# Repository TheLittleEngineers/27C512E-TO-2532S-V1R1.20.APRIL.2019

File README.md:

# 27C512E-TO-2532S-V1R1.20.APRIL.2019
<p align="center">
TheLittleEngineers.org-27C512E-TO-2532S-V1R1.20.APRIL.2019
27C512 E.P.R.O.M. TO TMS2532 SOCKET CONVERTER.
(C) 20 April 2019 and 01 June 2019 by: Robert Allen Turner
http://www.TheLittleEngineers.org/
https://github.com/TheLittleEngineers
</p>
<p align="justify">
This product is intended to allow a 27512 or 27C512 EPROM to be placed into a TMS2532 EPROM socket. The 27512 is divided into 16 banks of 4Kbytes via the four jumpers at the bottom of the socket.

Released under a Creative Commons Attribution-ShareAlike 4.0 International (CC BY-SA 4.0) License, 01 June 2019 In Memory of my Father, Robert Embry Turner, 1945 - 2019. Rest In Peace. I LOVE YOU DAD!
</p>
<p align="center">
Archive name: "TheLittleEngineers.org-27C512E-TO-2532S-V1R1.20.APRIL.2019"
</p>
This is an update to the "TheLittleEngineers.org-27C512E-TO-2532S-V1R0.20.APRIL.2019" repository which resides at this url:
https://github.com/TheLittleEngineers/27C512E-TO-2532S-V1R0
This update was made due to the fact that I was not very pleased with the initial Printed Circuit Boards that resulted from the original design. Although functional, the production of the Printed Circuit Boards was inconsistent between different manufacturers. This was due to a problem in the dimension layer of the original design and so I have created this new design to eliminate the inconsistencies.

This version should provide much better results.

Please note: This is derived from an original design by "Little" John Eric and/or his father "Big" John Robert (J.R.) by "Uncle" Robert Allen. It should be thoroughly scrutinized and verified prior to actual use of any kind. DISCLAIMER: The following article is provided for informational purposes only. Any attempt to modify your computer without the proper skills to do so may void your computer. Any attempt to modify your computer without unplugging it first may void you. This Information is provided "as-is" with no guarantee of fitness for any purpose, either explicit or implied. We disclaim any and all responsibility for losses incurred through the use of this information. By using this information, you are deemed to have accepted these conditions of use, and you agree NOT to sue us. CLARIFICATION: The above disclaimer states as plainly as possible that if you decide to make use of any of the information contained within this document that you do so at your own risk. Designing hardware for the CoCo (ColorComputer) and other vintage hardware is a hobby of ours and is not motivated by any desire of profits. As this is a not for profit venture, obviously we can't afford not to disclaim the use of this information.

The GitHub home of this project is available at the following url:
https://github.com/TheLittleEngineers/27C512E-TO-2532S-V1R1.20.APRIL.2019

This design is available at OSHPark with the following urls:
https://oshpark.com/shared_projects/JmUiHyi1 (EAGLE .brd)
https://oshpark.com/shared_projects/4RvjjYdM (KiCAD .kicad_pcb)
Note that the KiCAD version has been imported using the EAGLE import function of the Version 5.x of KiCAD. As such, it may be potentially problematic.

<!DOCTYPE html>
<html>
<head>

<meta name="Author" content="Robert &quot;The R.A.T.&quot; Allen Turner">
<meta name="GENERATOR" content="Tandy Radio Shack TRS-80 Color Computer 3">
<meta name="ProgId" content="TeleWriter-128.by.Bob.Van.der.Poel.for.Cognitec">
<meta http-equiv="Content-Type" content="text/html; charset=UTF-8">
<meta http-equiv="Content-Language" content="en-us">
<meta name="viewport" content="width=device-width, initial-scale=1">
<!--
<!meta http-equiv="Content-Type" content="text/html; charset=windows-1252">
This HTML is a veritable train wreck, however, it seems to get the job done on 24 September 2020 and beyond
-->

</head>

<body style="background-color:WhiteSmoke;">

<!-- Top Row -->
<center>
<h3 style="text-align: center; color: Black;">This page created: May 26, 2019, last updated: September 24, 2020. 
</center>
<p align="center">
<font size="6"><a href="http://www.TheLittleEngineers.org/" target="_blank">The</a> <a href="http://www.TheLittleEngineers.org/" target="_blank">Little</a> <a href="http://www.TheLittleEngineers.org/" target="_blank">Engineers</a> in conjunction with <a href="http://www.RetroATX.com" target="_blank">Retro</a><u>-</u><a href="http://www.Retro-ATX.com" target="_blank">ATX</a><br></font>
<font size="5"><em><b><a href="https://www.facebook.com/OurLittleEngineers/" target="_blank">Pulling</a> <a href="https://www.facebook.com/groups/985537051651794/" target="_blank">The</a> <a href="https://www.facebook.com/groups/566741160795144/" target="_blank">Past</a> <a href="https://www.facebook.com/TheLittleEngineers.org" target="_blank">Into</a> <a href="https://www.facebook.com/tincansandducttape/" target="_blank">The</a> <a href="https://www.facebook.com/Tin-Cans-Duct-Tape-728969003939754/" target="_blank">Present</a> <a href="https://www.facebook.com/groups/1654785514796788/" target="_blank">For</a> <a href="https://www.facebook.com/groups/1828354620822631/" target="_blank">The</a> <a href="https://www.facebook.com/groups/1451396811790867/" target="_blank">Future</a></b></em><br></font>
</p>
<p align="justify"><a href="http://www.TheLittleEngineers.org/" target="_blank">The</a> <a href="http://www.TheLittleEngineers.org/" target="_blank">Little</a> <a href="http://www.TheLittleEngineers.org/" target="_blank">Engineers</a> is a project began in 2011 by <a href="mailto:TheLittleEngineers@OutLook.com" target="_blank">Robert</a> <a href="mailto:LittleEngineer_RAT@OutLook.com" target="_blank">Allen</a> <a href="mailto:OurLittleEngineers@gMail.com" target="_blank">Turner</a> (hereafter, <a href="mailto:LittleEngineer.RAT@gMail.com" target="_blank">I</a>, <a href="mailto:TinCansAndDuctTape@gMail.com" target="_blank">Me</a>, <a href="mailto:CannedLogic@gMail.com" target="_blank">My</a>, <a href="mailto:TinCansAndDuctTape@OutLook.com" target="_blank">Author</a>, or <a href="mailto:LittleEngineer.RAT@OutLook.com" target="_blank">&quot;The R.A.T.&quot;</a>), for the benefit of foster children and their families (foster and biological). The original intent was simply to provide a means, in the form of donated cameras, of creating videos with the foster families such that the biological parents did not completely miss out on their children growing up. Providing simple to construct kits (electronics, arts, crafts, etcetera) seemed a logical choice as subject matter for such videos and these types of activities have the benefit of being educational. It is thus that those types of projects are primarily what <a href="mailto:LittleEngineer.RAT@OutLook.com" target="_blank">I</a> attempt to develop for use in such videos. This is a difficult, time consuming and expensive undertaking. Each case must be handled on an individual basis and any such videos and communications must be scrutinized and approved on a per case basis by the case workers, et alia in charge. Although this makes such an undertaking extremely difficult, it is a necessity in order to protect the children. Some are, after all, being protected from abusive family members and so there has to be a very strict set of protocols in place. This has prevented me from fully launching <a href="https://www.facebook.com/OurLittleEngineers/" target="_blank">The</a> <a href="https://www.facebook.com/groups/985537051651794/" target="_blank">Little</a> <a href="https://www.facebook.com/TheLittleEngineers.org" target="_blank">Engineers</a> over the past eight years, but I remain fully committed to the project with the intent of seeing it through to a fully operational entity.
</p>
<p align="justify"><a href="http://www.RetroATX.com" target="_blank">Retro</a><u>-</u><a href="http://www.Retro-ATX.com" target="_blank">ATX</a> was conceived with the sole purpose of creating &quot;ATX form factor&quot; versions of various <em>classic</em> and <i>vintage</i> computing and other systems. Such a system might be an Altair 8800 &quot;clone&quot; in an ATX or &micro;ATX form factor. Certainly, a system compatible with the Tandy Radio Shack TRS-80 Model II, 12, 16 and 6000 line of computers is planned, as are ATX or &micro;ATX versions of the following systems:<ul align="justify"><li align="justify">Sinclair QL</li><li align="justify">Dragon D64 and D200</li><li align="justify">Dragon Alpha</li><li align="justify">Dragon Beta</li><li align="justify">Tandy Color Computer 3</li><li align="justify">Mattel Intellivision &quot;Keyboard Component&quot;</li><li align="justify">Aamber Pegasys</li><li align="justify">MicroBox ][</li><li align="justify">Various Frank Hogg Laboratories Systems, including:<ul align="justify"><li align="justify">FHL &quot;K-Buss&quot; backplanes of many sizes and configurations</li><li align="justify">FHL Tomcat Series, including:<ul align="justify"><li align="justify">FHL TC-9 6809 CPU board</li><li align="justify">FHL TC-9 I/O board</li><li align="justify">FHL TC-70 68070 CPU board</li><li align="justify">FHL TC-70 I/O and all other boards</li></ul></li></ul></li><li align="justify">GIMIX 6800/6809 Series Motherboards</li><li align="justify">GIMIX 6800/6809 Series CPU boards</li><li align="justify">GIMIX 6800/6809 Series Peripheral Cards</li><li align="justify">SWTPC 6800/6809 Series Motherboards</li><li align="justify">SWTPC 6800/6809 Series CPU boards</li><li align="justify">SWTPC 6800/6809 Series Peripheral Cards</li></ul>
</p>
<p align="justify">The above list represents just some of the systems that are planned for reimplementation by <a href="http://www.RetroATX.com" target="_blank">Retro</a><u>-</u><a href="http://www.Retro-ATX.com" target="_blank">ATX</a>. Any suggestions for other systems and features are welcomed. The MicroBox ][, Aamber Pegasus and Frank Hogg Laboratory systems are a priority at present, although this may change based upon feedback received. Undertaking any one of the above projects is a monumental task, requiring the expenditure of many hours of work and yet we fully intend to complete each and every one of those projects as time and resources allow. It is very unlikely that we will be able to complete all of these projects without the assistance of the many members of the <em>&quot;Vintage Computing Community&quot;.</em> We are in dire need of donations of any of the following items:<ul align="justify"><li align="justify">SCHEMATICS, documentations, Theory of Operations, etcetera of any and all of the above listed equipment</li><li align="justify">Any of the above hardware and peripherals that you may no longer have need of, functional or not</li><li align="justify">Your expertise, experience, opinions, engineering and other skills, etcetera</li></ul><b>Any items of interest, from the above list(s) or otherwise may be delivered to:</b>
</p>
<p align="center"><b>The Little Engineers Project/RetroATX.com<br>C/O Robert Turner<br>69 Lilly Lane<br>Pell City, AL 35125</b></p>
<p align="justify">Your continued encouragement and <a href="#support">support</a> are greatly appreciated. Other methods of <a href="#digitalcurrency">potential</a> <a href="#patreon">support</a> are contained <a href="#support">further</a> into this <a href="#support">document</a>. Thank You and God Bless.</p>
 
<p align="justify"><b>The logos, names and other material relating to <a href="https://www.facebook.com/OurLittleEngineers/" target="_blank">The</a> <a href="https://www.facebook.com/groups/985537051651794/" target="_blank">Little</a> <a href="https://www.facebook.com/TheLittleEngineers.org" target="_blank">Engineers</a>, <a href="http://www.TheLittleEngineers.org/" target="_blank">TheLittleEngineers.org</a>, <a href="http://www.RoboCircuits.org/" target="_blank">RoboCircuits</a>, <a href="http://www.RoboCircuits.org/" target="_blank">RoboCircuits.org</a>, <a href="https://www.facebook.com/tincansandducttape/" target="_blank">Tin</a> <a href="https://www.facebook.com/groups/1654785514796788/" target="_blank">Cans</a> <a href="https://www.facebook.com/Tin-Cans-Duct-Tape-728969003939754/" target="_blank">And</a> <a href="https://www.facebook.com/groups/1828354620822631/" target="_blank">Duct</a> <a href="https://www.facebook.com/groups/228910954180459/" target="_blank">Tape</a>, <a href="http://www.tincansandducttape.com/" target="_blank">TinCansAndDuctTape.com</a>, <a href="http://www.tcadt.com/" target="_blank">TCADT</a>, <a href="http://www.tcadt.com/" target="_blank">TCADT.com</a>, <a href="http://www.CannedLogic.com/" target="_blank">Canned Logic</a>, <a href="http://www.CannedLogic.com/" target="_blank">CannedLogic.com</a>, <a href="http://www.RetroATX.com/" target="_blank">RetroATX</a>, <a href="http://www.RetroATX.com/" target="_blank">RetroATX.com</a>, <a href="http://www.Retro-ATX.com/" target="_blank">Retro-ATX</a>, <a href="http://www.Retro-ATX.com/" target="_blank">Retro-ATX.com</a>, <a href="http://www.TheLittleEngineers.org/pages/reference/20200112/ZombieSoftwareSystems" target="_blank">Zombie</a> <a href="http://www.TheLittleEngineers.org/pages/reference/20200112/ZombieSoftwareSystems" target="_blank">Software</a> <a href="http://www.TheLittleEngineers.org/pages/reference/20200112/ZombieSoftwareSystems" target="_blank">Systems</a>, <a href="http://www.TheLittleEngineers.org/pages/reference/20200112/BinarySystems" target="_blank">Binary</a> <a href="http://www.TheLittleEngineers.org/pages/reference/20200112/BinarySystems" target="_blank">Systems</a>, <a href="http://www.GIMEchip.com/" target="_blank">GIMEchip</a> and <a href="http://www.GIMEchip.com/" target="_blank">GIMEchip.com</a> are the sole property of <a href="https://www.facebook.com/TheLittleEngineers.org" target="_blank">Robert</a> <a href="mailto:TheLittleEngineers@OutLook.com" target="_blank">Allen</a> <a href="https://www.facebook.com/TinCansDuctTape" target="_blank">Turner</a> with <em>All Rights Reserved</em>.</b> The rights to the <a href="http://www.GIMEchip.com/" target="_blank">GIMEchip.com</a> domain and <a href="https://www.github.com/TheLittleEngineers?tab=repositories" target="_blank">products</a> were acquired by the <a href="https://www.facebook.com/TheLittleEngineers.org" target="_blank">author</a> on 25 December 2018 from my brother and his son, the former owners/operators of <a href="http://www.GIMEchip.com/" target="_blank">GIMEchip.com</a>. Please note that the author is unable to answer any inquiries, including those of support or otherwise, in relation to <a href="http://www.GIMEchip.com/" target="_blank">GIMEchip.com</a> prior to his acquisition of same on 25 December 2018. This is primarily because the author posseses no knowlege of the site operation prior to that time. Although I have been provided with a large number of files that were originally contained on the website, it is unlikely that I will resurrect <a href="http://www.GIMEchip.com/" target="_blank">GIMEchip.com</a> other than perhaps as a <a href="http://www.TheLittleEngineers.org/WebSites/GIMEchip/" target="_blank">page</a> on <a href="http://www.TheLittleEngineers.org/WebSites/GIMEchip/" target="_blank">one</a> of my other websites. These files are mostly HTML page files and C.A.D. files of the products designed and developed by my nephew and his father, and very little else. As part of the acquisition agreement, all products previously produced by <a href="http://www.GIMEchip.com/" target="_blank">GIMEchip.com</a> are to be released under a <a href="http://www.TheLittleEngineers.org/pages/reference/20200112/CreativeCommons/CCBYSA.htm" target="_blank">Creative Commons Attribution-ShareAlike 4.0 International</a> <a href="http://www.TheLittleEngineers.org/pages/reference/20200112/CreativeCommons/CCBYSALegalCode.htm" target="_blank">(CC BY-SA 4.0)</a> License, as time and resources permit. Although many of these projects are somewhat interesting, none of them seem particularly useful or revolutionary.</p>
<p align="center">
<font size="6">DISCLAIMER:<br></font>
<font size="5"><em>Please Read Carefully.<br></em></font>
</p>
<p align="justify">This information is provided for informational purposes only. Any attempt to modify your equipment (including, but not limited to kit assembly) without the proper skills to do so may void your equipment. Any attempt to modify your equipment without unplugging it first may void you. This Information is provided "as-is" with no guarantee of fitness for any purpose, either explicit or implied. We disclaim any and all responsibility for losses incurred through the use of this information. Included with this information may be one or more C.A.D. Libraries, such as for E.A.G.L.E., KiCAD, etcetera. Any such C.A.D. libraries, except as may be noted are released under a <a href="http://www.TheLittleEngineers.org/pages/reference/20200112/CreativeCommons/CCBYSA.htm" target="_blank">Creative Commons Attribution-ShareAlike 4.0 International</a> <a href="http://www.TheLittleEngineers.org/pages/reference/20200112/CreativeCommons/CCBYSALegalCode.htm" target="_blank">(CC BY-SA 4.0)</a> License. You may use these libraries in your own projects, however, please take note that we CANNOT guarantee the accuracy of the components (nor any part of these libraries and/or information). We make NO guarantees that the components, footprints or schematic symbols contained in these libraries are flawless, and we make no promises of fitness for production, prototyping or any other purpose. These libraries and/or information are provided for informational purposes only, and are used at your own discretion. By downloading these libraries and/or information, you agree that we cannot be held responsible for faulty PCBs (Printed Circuit Boards). <b>You should always check the footprints with a 1:1 printout.</b> Neither Robert Allen Turner, <a href="https://www.facebook.com/OurLittleEngineers/" target="_blank">The</a> <a href="https://www.facebook.com/groups/985537051651794/" target="_blank">Little</a> <a href="https://www.facebook.com/TheLittleEngineers.org" target="_blank">Engineers</a>, <a href="http://www.TheLittleEngineers.org/" target="_blank">TheLittleEngineers.org</a>, <a href="https://www.facebook.com/tincansandducttape/" target="_blank">Tin</a> <a href="https://www.facebook.com/groups/1654785514796788/" target="_blank">Cans</a> <a href="https://www.facebook.com/Tin-Cans-Duct-Tape-728969003939754/" target="_blank">And</a> <a href="https://www.facebook.com/groups/1828354620822631/" target="_blank">Duct</a> <a href="https://www.facebook.com/groups/228910954180459/" target="_blank">Tape</a>, <a href="http://www.tincansandducttape.com/" target="_blank">TinCansAndDuctTape.com</a>, <a href="http://www.tcadt.com/" target="_blank">TCADT</a>, <a href="http://www.tcadt.com/" target="_blank">TCADT.com</a>, <a href="http://www.CannedLogic.com/" target="_blank">Canned Logic</a>, <a href="http://www.CannedLogic.com/" target="_blank">CannedLogic.com</a>, <a href="http://www.RetroATX.com/" target="_blank">RetroATX</a>, <a href="http://www.RetroATX.com/" target="_blank">RetroATX.com</a>, <a href="http://www.Retro-ATX.com/" target="_blank">Retro-ATX</a>, <a href="http://www.Retro-ATX.com/" target="_blank">Retro-ATX.com</a>, <a href="http://www.RoboCircuits.org/" target="_blank">RoboCircuits</a>, <a href="http://www.RoboCircuits.org/" target="_blank">RoboCircuits.org</a>, <a href="http://www.TheLittleEngineers.org/pages/reference/20200112/ZombieSoftwareSystems" target="_blank">Zombie</a> <a href="http://www.TheLittleEngineers.org/pages/reference/20200112/ZombieSoftwareSystems" target="_blank">Software</a> <a href="http://www.TheLittleEngineers.org/pages/reference/20200112/ZombieSoftwareSystems" target="_blank">Systems</a>, <a href="http://www.TheLittleEngineers.org/pages/reference/20200112/BinarySystems" target="_blank">Binary</a> <a href="http://www.TheLittleEngineers.org/pages/reference/20200112/BinarySystems" target="_blank">Systems</a>, <a href="http://www.GIMEchip.com/" target="_blank">GIMEchip</a>, <a href="http://www.GIMEchip.com/" target="_blank">GIMEchip.com</a>, nor anyone affiliated with same shall be held responsible for any outcome resulting from the usage of these files and/or information. Should any errors be found, please contact us at one of the provided email addresses and we will attempt to repair them. Unless otherwise noted, content of this library and other information is licensed under a <a href="http://www.TheLittleEngineers.org/pages/reference/20200112/CreativeCommons/CCBYSA.htm" target="_blank">Creative Commons Attribution-ShareAlike 4.0 International</a> <a href="http://www.TheLittleEngineers.org/pages/reference/20200112/CreativeCommons/CCBYSALegalCode.htm" target="_blank">(CC BY-SA 4.0)</a> License, <b><em>in memory of my Father</em>, <i>Robert Embry Turner</i>, 1945-2019 - I LOVE AND MISS YOU DAD! <em>Rest In Peace</em></b>. By using this information, you are deemed to have accepted these terms and conditions of use, and you agree NOT to sue us.</p>
<p align="center"><font size="5"><em>CLARIFICATION:</em></font></p>
<p align="justify">The disclaimer states as plainly as possible that if you decide to make use of any of the information contained within this document and/or any of the accompanying files that you do so at your own risk. Designing products for the <a href="http://www.TheLittleEngineers.org/" target="_blank">Little Engineers Project</a> and/or affiliates is not motivated by any desire of profits. As this is a not for profit venture, obviously we can't afford not to disclaim the use of this information. Thank You for your understanding and acceptance of these terms of use.</p>
<hr>
<!-- /Top Row -->

<!-- Top Left Column -->
<div class="row" style="background-color:WhiteSmoke;" align="center">
<div class="column" style="background-color:WhiteSmoke;" align="center">
<h2 align="center"><a href="http://www.TheLittleEngineers.org/pages/reference/20200103/IMDb/WhoAmI.htm" target="_blank">Who Am I?</a><br>Hint: I'm Not <a href="http://www.TheLittleEngineers.org/pages/reference/20200103/IMDb/JackieChan.htm" target="_blank">Jackie Chan</a>.<br>I Did Enjoy That Film Immensely.</h2>
<p align="justify">The headline of this paragraph is merely an attempt at humor while allowing me the opportunity to mention a <a href="http://www.TheLittleEngineers.org/pages/reference/20200103/IMDb/WhoAmI.htm" target="_blank">film</a> that my son and I quite thoroughly enjoyed when it was released during his childhood in 1998, leading to his eventual love of <a href="http://www.TheLittleEngineers.org/pages/reference/20200112/IMDb/JackieChanAdventures.htm" target="_blank">&quot;The Jackie Chan Adventures&quot;</a> animated series, which would be released some two years later in 2000. Most of the world seemed to be concerned with the overhyped <a href="http://www.TheLittleEngineers.org/pages/reference/20200112/Y2K/Y2KBug.htm" target="_blank">&quot;Y2K Bug&quot;</a> and we were just watching <a href="http://www.TheLittleEngineers.org/pages/reference/20200103/IMDb/JackieChan.htm" target="_blank">Jackie</a> <a href="http://www.TheLittleEngineers.org/pages/reference/20200112/IMDb/JackieChanAdventures.htm" target="_blank">Chan</a> and enjoying our lives while playing <a href="http://www.TheLittleEngineers.org/pages/reference/20200112/NickMarentes/CosmicAmbush.htm" target="_blank">&quot;Cosmic Ambush&quot;</a> and <a href="http://www.TheLittleEngineers.org/pages/reference/20200112/GoSub/TheCrystalCityGitHub.htm" target="_blank">&quot;</a><a href="http://www.TheLittleEngineers.org/pages/reference/20200112/GoSub/GoSubZenixTheCrystalCity.htm" target="_blank">The</a> <a href="http://www.TheLittleEngineers.org/pages/reference/20200112/GoSub/JeremySpillerResume.htm" target="_blank">Crystal</a> <a href="http://www.TheLittleEngineers.org/pages/reference/20200112/GoSub/SixtyFramesPerSecondOrBust.htm" target="_blank">City</a><a href="http://www.TheLittleEngineers.org/pages/reference/20200112/GoSub/TheCrystalCityGitHub.htm" target="_blank">&quot;</a> on our 512K CoCo 3. The following text serves as a general Introduction to <a href="mailto:TheLittleEngineers@OutLook.com" target="_blank">Robert</a> <a href="mailto:LittleEngineer_RAT@OutLook.com" target="_blank">&quot;The R.A.T.&quot;</a> <a href="mailto:OurLittleEngineers@gMail.com" target="_blank">Allen</a> <a href="mailto:LittleEngineer.RAT@gMail.com" target="_blank">Turner</a>, <a href="http://www.TheLittleEngineers.org/pages/reference/20200112/ZombieSoftwareSystems" target="_blank">Zombie</a> <a href="http://www.TheLittleEngineers.org/pages/reference/20200112/ZombieSoftwareSystems" target="_blank">Software</a> <a href="http://www.TheLittleEngineers.org/pages/reference/20200112/ZombieSoftwareSystems" target="_blank">Systems</a>, <a href="http://www.TheLittleEngineers.org/pages/reference/20200112/BinarySystems" target="_blank">Binary</a> <a href="http://www.TheLittleEngineers.org/pages/reference/20200112/BinarySystems" target="_blank">Systems</a>, <a href="https://www.facebook.com/OurLittleEngineers/" target="_blank">The</a> <a href="https://www.facebook.com/groups/985537051651794/" target="_blank">Little</a> <a href="https://www.facebook.com/TheLittleEngineers.org" target="_blank">Engineers</a>, <a href="http://www.TheLittleEngineers.org/" target="_blank">TheLittleEngineers.org</a>, <a href="https://www.facebook.com/tincansandducttape/" target="_blank">Tin</a> <a href="https://www.facebook.com/groups/1654785514796788/" target="_blank">Cans</a> <a href="https://www.facebook.com/Tin-Cans-Duct-Tape-728969003939754/" target="_blank">And</a> <a href="https://www.facebook.com/groups/1828354620822631/" target="_blank">Duct</a> <a href="https://www.facebook.com/groups/228910954180459/" target="_blank">Tape</a>, <a href="http://www.tincansandducttape.com/" target="_blank">TinCansAndDuctTape.com</a>, <a href="http://www.tcadt.com/" target="_blank">TCADT</a>, <a href="http://www.tcadt.com/" target="_blank">TCADT.com</a>, <a href="http://www.CannedLogic.com/" target="_blank">Canned Logic</a>, <a href="http://www.CannedLogic.com/" target="_blank">CannedLogic.com</a>, <a href="http://www.RetroATX.com/" target="_blank">RetroATX</a>, <a href="http://www.RetroATX.com/" target="_blank">RetroATX.com</a>, <a href="http://www.Retro-ATX.com/" target="_blank">Retro-ATX</a>, <a href="http://www.Retro-ATX.com/" target="_blank">Retro-ATX.com</a>, <a href="http://www.RoboCircuits.org/" target="_blank">RoboCircuits</a>, <a href="http://www.RoboCircuits.org/" target="_blank">RoboCircuits.org</a>, <a href="http://www.GIMEchip.com/" target="_blank">GIMEchip</a> and <a href="http://www.GIMEchip.com/" target="_blank">GIMEchip.com</a>. Please note that the <a href="http://www.GIMEchip.com/" target="_blank">GIMEchip.com</a> domain was acquired by <a href="mailto:TheLittleEngineers@OutLook.com" target="_blank">Robert</a> <a href="mailto:LittleEngineer_RAT@OutLook.com" target="_blank">&quot;The R.A.T.&quot;</a> <a href="mailto:OurLittleEngineers@gMail.com" target="_blank">Allen</a> <a href="mailto:LittleEngineer.RAT@gMail.com" target="_blank">Turner</a> on December 25, 2018 from the prior owners, who happen to be his brother (J.R. a.k.a. John Robert a.k.a. &quot;Big John&quot;) and nephew (J.E. a.k.a. John Eric a.k.a. &quot;Little John&quot;). As such, <a href="mailto:LittleEngineer.RAT@OutLook.com" target="_blank">&quot;The R.A.T.&quot;</a> is unable to answer any inquiries regarding any products or services of <a href="http://www.GIMEchip.com/" target="_blank">GIMEchip.com</a> prior to that date simply because I have no knowledge of the site. I have attempted to utilize the <a href="http://www.TheLittleEngineers.org/pages/reference/20200103/GIMEchip/GIMEchipWayBackMachine.htm" target="_blank">Internet Archive WayBack Machine</a> to have a look at the <a href="http://www.TheLittleEngineers.org/pages/reference/20200103/GIMEchip/GIMEchipWayBackMachine.htm" target="_blank">site</a> at various stages of existence, but there seems to be very little there as of the date of this writing (April 10, 2019). <a href="mailto:LittleEngineer_RAT@OutLook.com" target="_blank">&quot;The R.A.T.&quot;</a> has also acquired the rights to all products previously produced by <a href="http://www.GIMEchip.com/" target="_blank">GIMEchip.com</a> and its previous owners. As part of the acquisition agreement, all of those products will be released as open source, under a <a href="http://www.TheLittleEngineers.org/pages/reference/20200112/CreativeCommons/CCBYSA.htm" target="_blank">Creative Commons Attribution-ShareAlike 4.0 International</a> <a href="http://www.TheLittleEngineers.org/pages/reference/20200112/CreativeCommons/CCBYSALegalCode.htm" target="_blank">(CC BY-SA 4.0)</a> License, as time and resources permit. Note that some of these products were previously released by my brother under an <a href="http://www.TheLittleEngineers.org/pages/reference/20200112/CreativeCommons/OSHWA.htm" target="_blank">Open Source Hardware License</a> and all of those releases remain available under that license. Making certain that any given product meets all of the requirements necessary for the <a href="http://www.TheLittleEngineers.org/pages/reference/20200112/CreativeCommons/OSHWA.htm" target="_blank">OSHWA</a> license is a time consuming task when preparing older archives for release and so I have decided to utilize a <a href="http://www.TheLittleEngineers.org/pages/reference/20200112/CreativeCommons/CCBYSA.htm" target="_blank">Creative Commons Attribution-ShareAlike 4.0 International</a> <a href="http://www.TheLittleEngineers.org/pages/reference/20200112/CreativeCommons/CCBYSALegalCode.htm" target="_blank">(CC BY-SA 4.0)</a> License for any releases prepared by myself. This should allow you to utilize the releases in almost any desired manner, including commercial, within the terms of the license.</p>
<h3 align="center">Introducing <a href="mailto:TheLittleEngineers@OutLook.com" target="_blank">T</a><a href="mailto:LittleEngineer_RAT@OutLook.com" target="_blank">h</a><a href="mailto:OurLittleEngineers@gMail.com" target="_blank">e</a> <a href="mailto:LittleEngineer.RAT@gMail.com" target="_blank">&quot;</a><a href="mailto:TinCansAndDuctTape@gMail.com" target="_blank">R</a><a href="mailto:CannedLogic@gMail.com" target="_blank">.</a><a href="mailto:TinCansAndDuctTape@OutLook.com" target="_blank">A</a><a href="mailto:LittleEngineer.RAT@OutLook.com" target="_blank">.</a><a href="mailto:TheLittleEngineers@OutLook.com" target="_blank">T</a><a href="mailto:LittleEngineer_RAT@OutLook.com" target="_blank">.</a><a href="mailto:OurLittleEngineers@gMail.com" target="_blank">&quot;</a></h3>
<p align="justify">I have started writing this introduction numerous times only to get sidetracked and derailed. Hopefully, I will be able to properly introduce myself this time. I will begin at the acquisition of my first personal computer, a Sinclair ZX81 Issue 3, produced by Timex and sold as the TS1000 (Timex Sinclair 1000 or T/S1000). This would be March 30, 1982 - My fourteenth birthday. My parents presented me with a Timex Sinclair 1000 (TS1000) computer, after much begging and pleading. The TS1000 is a ZX81 with a few differences: 2K of RAM, an [ENTER] key instead of [NEW LINE] or [N/L] and Timex branding. I had wanted a computer for so long, and Sir Clive Sinclair succeeded in making it affordable. Timex made it even more affordable as the TS1000 was placed on sale for $59.99 at the local "Big B" drug store, at the time, a division of Brunos Corporation (Food World, Food Fair, Consumer Warehouse, etcetera). I was ecstatic - I finally had a computer, and as limited as it was, I still mamaged to learn a great deal from that machine. This experience with the ZX81 (T/S1000) led to the creation of Zombie Software Systems, my first computer venture. When Timex announced the Timex Sinclair 2068 (TS2068) after canceling the TS2000 (a 48K Spectrum clone), I knew that I wanted it to be my next computer and my parents agreed to buy it for me for Christmas of 1983. Then, it happened: I walked into the local franchised Radio Shack store, operated at the time by Cisco Auto Parts, and there, on display right next to the entrance, was the newly introduced Color Computer 2 with 16K of RAM and Extended Color BASIC. It took mere moments for me to fall in love with that machine and I asked my parents for the Color Computer 2 instead of the TS2068. They placed it on lay-a-way as Christmas approached. It was eventually paid off and sat under the Christmas tree until Christmas Evening of 1983. They allowed me to open it on Christmas Evening and I was up all night working through the programs in the manuals. It was wonderful. This led to the creation of Binary Systems, my second computer venture. Eventually, I came across an advertisement in Radio-Electronics from a company by the name of Unicorn Electronics (a company that remains in business until this very day). They had a set of 4164 Dynamic RAM chips with a 150nS access time for, I think $9.95 (although I seem to remember $1.50 each, so perhaps it was $1.50 per chip or 8/$9.95). The chips were used but tested pulls. I ordered them, along with a bag of keyboard switches (intended to be used for building a better keyboard for my TS1000 and adding four function keys to the CoCo 2). When they arrived, I opened the case of my Color Computer 2, installed the 64K chips, soldered in the <b>W1</b> <em>jumper</em> and voila - I had a 64K ECB Color Computer 2. Although other systems of the time had better graphics and sound, the Color Computer line of systems by Radio Shack, a division of Tandy Corporation, would become (and remain) my favorite computers of all time. In fact, I still use them to this very day, having kept one Color Computer 3 (CoCo 3) when I passed my vintage computing collection to my brother, J.R. (John Robert) who then passed it on to his son, &quot;Little John&quot; (John Eric), but I will get to that after a brief reminiscence of ZSS and BS, as follows:</p>
<h3 align="center">ZSS or Zombie Software Systems:</h3>
<p align="justify">Zombie Software Systems was formed on my fourteenth birthday, 30 March 1982, as a sole proprietorship supporting the Timex and Sinclair computer systems.</p>
<h3 align="center">Supported systems initially included:</h3>
<p align="justify"><ul align="justify">
<li align="justify">Sinclair ZX80</li>
<li align="justify">Sinclair ZX81</li>
<li align="justify">Timex Sinclair 1000</li>
</ul>
<h3 align="center">Support was eventually added for:</h3>
<ul align="justify">
<li align="justify">Timex Sinclair 1500</li>
<li align="justify">The PC-8300 "Your Computer"</li>
<li align="justify">Sinclair Spectrum (All Versions)</li>
<li align="justify">Timex Sinclair 2068</li>
<li align="justify">Sinclair QL</li>
</ul>
<p align="justify">By 1991, and in conjunction with Binary Systems, support had been added for machines from Mattel, Atari, Tomy, Texas Instruments, Tandy Radio Shack, Commodore and many others.</p>
<h3 align="center">BS or Binary Systems:</h3>
<p align="justify">Binary Systems was formed on 23 December 1983, as a sole proprietorship supporting the Tandy Radio Shack computer systems.
<h3 align="center">Supported systems initially included:</h3>
<ul align="justify">
<li align="justify">TRS-80 Color Computer (CoCo 1)</li>
<li align="justify">Tandy Data Products TDP-100</li>
<li align="justify">TRS-80 Color Computer 2 (CoCo 2)</li>
<li align="justify">Dragon Data Dragon 32</li>
<li align="justify">Tano Dragon 64</li>
<li align="justify">TRS-80 Model I</li>
</ul>
</div>
<!-- /Top Left Column -->

<!-- Top Right Column -->
<div class="column" style="background-color:WhiteSmoke;" align="center">
<h3 align="center">Support was eventually added for:</h3>
<ul align="justify">
<li align="justify">TRS-80 Model III</li>
<li align="justify">TRS-80 Model IV</li>
<li align="justify">TRS-80 Model 4/4P</li>
<li align="justify">Tandy Color Computer 3</li>
</ul>
<p align="justify">By 1991, and in conjunction with Zombie Software Systems, support had been added for machines from Mattel, Atari, Tomy, Texas Instruments, Sinclair, Commodore, Amstrad, Kaypro and many others. The operation of Zombie Software Systems and Binary Systems was a labor of love more than anything else, as it never made a profit, but it was fun and remains among the best memories of my youth and early adulthood and I am thankful that the stroke
(see below) did not take these memories from me.</p>
<p align="justify">I continued to support these vintage machines until 2007 when I suffered a stroke. At that point, I passed operations on to my son, John (he and his cousin share both
the same name and same date of birth through a very odd coincidence). My son eventually made a mess of things and finally moved on to other hobbies. A side effect of the stroke was that I lost almost all interest in
computers and electronics, vintage and otherwise. It was thus that I presented my entire collection of vintage computers and electronics to my brother J.R. (John Robert or &quot;Big John&quot;). He took the opportunity to bond
with his son, J.E. (John Eric or &quot;Little John&quot;). &quot;Little John&quot; was facing a number of health issues, but he jumped in with both feet, teaching himself all about the Color Computer and other systems. He began to develop
a plethora of hardware projects for the Color Computer and other vintage systems. The earliest of his designs were rubbish due to his lack of skill, but he appears to have learned rather quickly, producing some amazing
designs. I have taken it upon myself to "redo" his earliest works, hopefully producing manufacturable products from them. The first of his designs to receive the "redesign" treatment from me is the &quot;FlexiMIDI&quot;, &quot;FlexiROM&quot;
and &quot;FlexiBuffer&quot; projects. Those three designs were excellent in concept, but rubbish in practice due to his lack of circuit design skills at the time that he developed them. They are certainly worth the time and effort
to redesign. He would eventually become disillusioned and abandon the hobby altogether. This was, in no small part, due to hackers repeatedly taking down his website: <a href="http://www.GIMEchip.com/" target="_blank">GIMEchip.com</a>. They (the unknown hackers) eventually
compromised his eBay and PayPal accounts, rendering them completely useless. That was the straw that broke the camels back, so to speak. He (&quot;Little John&quot;) gave up and moved to Tennessee. He left everything with his
father, my brother, and asked that his father release all of his works as open source. J.R. made several valiant efforts to honor that request, but never fully succeeded in releasing all of the works of &quot;Little John&quot;.
Fast Forward almost a decade...</p>

<h3 align="center">The Beginning of a Family Tragedy:</h3>
<p align="justify">November of 2018, my father, Robert Embry Turner fell ill and was hospitalized. As Christmas approached, he remained in the hospital. Many family members visited and it came to pass that I reconnected with J.R. and &quot;Little John&quot;. They asked me if I would like to have my old vintage computing collection back. At first, I was hesitant and uninterested. As my fathers condition worsened, I began to remember how hard my father worked to buy me those first computers. Tons of memories, good and bad, began to flood my mind. I decided to accept their offer. In addition to the hardware and software, they presented me with the <a href="http://www.GIMEchip.com/" target="_blank">GIMEchip.com</a> domain name. This became my Christmas present from my brother and his son. &quot;Little John&quot; asked that I finish what his father started: the release of all of  &quot;Little John's&quot; work as open source. I reluctantly agreed, though I was unsure if I could ever manage the time and effort to do so. I honestly was not prepared to take on such a monumental task. Then, tragedy struck.
<br><br>
On the day of January 4, 2019, my father died as I held his hand in that hospital room. His death had quite a profound effect on me. I almost lost my job while trying to come to terms with never being able to speak to my father again. I eventually began to recover, to an extent, but I began to think of everything and everyone that I had lost over the years. For one thing, my own son, also named John Eric Turner, and I are estranged. We "speak" online, but I have not seen him in a very long time<a href="#son">*</a>. He was unable to be at the hospital and did not get to say goodbye to my father before he died. As mentioned, my son and his cousin are both named John Eric Turner, and there is a story behind it, however, for the moment, suffice it to say that they both were named In Memory of Jon-Erik Hexum, who died on the set of "Cover Up" on Friday, October 12, 1984. As my mind wandered, I thought of my mother in law, Sarah Ann Channell, who passed away on January 12, 2003 and my father in law, Frank Leon Channell, who passed away on August 23, 2003. Even though I was divorced from their daughter, they were still family and their deaths were very painful to me and my son. Indeed, their deaths affected my son in such a way that he never fully recovered and that is partially what eventually led to our falling out in 2007 or 2008 and the resulting estrangement. I am sure that my addled state after that stroke also played a hand in the troubles between my son and I because I became very difficult to be around. Thinking about Sarah and Frank caused me to really begin missing my son and, even more, my father. I then thought about my best friend from high school, David Ray Poe, who died on May 20, 2013. Eight days prior to his death, he had sent me an email that I did not see until after he died. That email was a single sentence: "Did you die?". You can perhaps imagine the effect that reading the message had on me. In reality, he would often send a message like that when he had not heard from me in a while. Another close friend from high school, Steve Allen Cox, died on September 6, 2016. As all of the thoughts of everything and everyone that I had lost flooded my mind, I began to spiral and was in peril of losing myself. I needed a distraction, something to keep my mind occupied and perhaps aid in my coming to terms with the death of my father. I found that distraction in the form of that vintage computing collection and the projects that &quot;Little John&quot; had created. It is for that reason alone that you are now reading this and seeing those products, which I have decided to release under a <a href="http://www.TheLittleEngineers.org/pages/reference/20200112/CreativeCommons/CCBYSA.htm" target="_blank">Creative Commons Attribution-ShareAlike 4.0 International</a> <a href="http://www.TheLittleEngineers.org/pages/reference/20200112/CreativeCommons/CCBYSALegalCode.htm" target="_blank">(CC BY-SA 4.0)</a> License. What this means is that you, or anyone else for that matter, may use the products in almost any way that you may desire, even commercially. I am doing all of this to honor the memory of my father, Robert Embry Turner, and everyone else that I have lost. I truly hope that these products provide much enjoyment to all who discover them. I should point out that I have absolutely no desire to revive the <a href="http://www.GIMEchip.com/" target="_blank">GIMEchip.com</a> website, primarily because I do not have all of the files necessary to recreate <a href="http://www.GIMEchip.com/" target="_blank">GIMEchip.com</a>. It is very likely that I will stumble across some or all of the <a href="http://www.GIMEchip.com/" target="_blank">GIMEchip.com</a> website files as I begin to inventory everything that was included with my 2018 Christmas gift from &quot;Big and Little John&quot;. I also DO NOT wish to invoke the ire of those hackers who targeted my nephew and destroyed his website, eBay and PayPal accounts. I will very likely, however, forward the <a href="http://www.GIMEchip.com/" target="_blank">GIMEchip.com</a> domain to a page on my <a href="http://www.TheLittleEngineers.org/" target="_blank">http://www.TheLittleEngineers.org/</a> website or perhaps I will forward it to the GitHub page - I am currently undecided.

So, there you have it - most of what I wanted to say about how I came to posses all of the works of my nephew and his father, as well as their domain name, <a href="http://www.GIMEchip.com/" target="_blank">GIMEchip.com</a>. In addition to releasing all of their products under a <a href="http://www.TheLittleEngineers.org/pages/reference/20200112/CreativeCommons/CCBYSA.htm" target="_blank">Creative Commons Attribution-ShareAlike 4.0 International</a> <a href="http://www.TheLittleEngineers.org/pages/reference/20200112/CreativeCommons/CCBYSALegalCode.htm" target="_blank">(CC BY-SA 4.0)</a> License, I will also be releasing all of the Zombie Software Systems and Binary Systems products under identical licensing terms.</p>
  </div>
  </div>
  <hr>
<!-- /Top Right Column -->
 
<!-- Center Row -->
<p align="center">
<font size="6">Is ALL of this really FREE?<br></font>
<font size="5"><em>YES!</em></font>
</p>
<p align="justify" id="support">
Everything contained in the GitHub Repositories for these projects is free to use, even commercially, in accordance with the terms of the <a href="http://www.TheLittleEngineers.org/pages/reference/20200112/CreativeCommons/CCBYSA.htm" target="_blank">Creative Commons Attribution-ShareAlike 4.0 International</a> <a href="http://www.TheLittleEngineers.org/pages/reference/20200112/CreativeCommons/CCBYSALegalCode.htm" target="_blank">(CC BY-SA 4.0)</a>License. The Amazon Kindle and Paperback Publications, however, are not licensed for redistribution and are only available to our Patrons as a free ".PDF" or for purchase from Amazon. These particular publications help to generate revenue that is used for further developmental efforts. It is not necessary to purchase these publications in order to make use of the GitHub Repositories, however, such purchases provide the funds necessary for the development of future products. The repositories contain all necessary information needed to construct, assemble and use the products described therein. If you would like to support our continued developmental efforts, the remaining paragraphs detail several methods that may be used to offer support of our work.

As stated, I have absolutely no intention of charging any fees whatsoever in regards to the use of these products. Anyone who so desires may manufacture and sell any of these products, though they must state specifically that they will be providing any and all support as may be required. However, If you would care to support my work, donations are happily accepted, whether they be in the form of funds, vintage computing equipment, tools, components, etcetera. I am always in need of such items. I specifically need PAL versions of the TRS80 Color Computer series (1,2 and 3) as well as NTSC/PAL Dragon D32, D64, D200, etcetera for developmental purposes. Monetary donations help to support the hosting needs of http://www.TheLittleEngineers.org/ as well as the development and manufacture of the prototype Printed Circuit Boards.

Perhaps the easiest and most beneficial method of supporting The Little Engineers (monetarily) would be by becoming a <a href="https://www.patreon.com/TheLittleEngineers" target="_blank">Patron</a> on <a href="https://www.patreon.com/TheLittleEngineers" target="_blank">Patreon</a>. The following are among the benefits offered to <a href="https://www.patreon.com/TheLittleEngineers" target="_blank">Patrons</a>. <a href="https://www.patreon.com/TheLittleEngineers" target="_blank">Patrons</a> will receive several exclusive benefits, such as:
<p align="justify" id="patreon"><ul align="justify">
<li align="justify">FREE copies of ANY of our detailed Theory of Operation and Assembly e-books relating to our projects.
</li>
<li align="justify">Random giveaways of bare Printed Circuit Boards (PCB's) developed by The Little Engineers.
</li>
<li align="justify">Random giveaways of Kits developed by The Little Engineers.
</li>
<li align="justify">Random giveaways of assembled projects developed by The Little Engineers.
</li>
<li align="justify">The opportunity to purchase various bare Printed Circuit Boards (PCB's) developed by The Little Engineers at discounts of up to 50% off.
</li>
<li align="justify">The opportunity to purchase various Kits developed by The Little Engineers at discounts of up to 50% off.
</li>
<li align="justify">The opportunity to purchase various assembled projects developed by The Little Engineers at discounts of up to 50% off.
</li>
</ul>
<p align="justify">
We will also be publishing detailed Theory of Operation and assembly manuals for all of our open source products in e-book and paperback formats. Purchases of these e-books and/or paperbacks helps to support The Little Engineers and our continued developmental efforts. Donations may also be made in almost any variety of digital currency, including, but not limited to, the following:</p>
<p align="justify" id="digitalcurrency"><ul align="justify">
<li align="justify">BitCoin (BTC):<br>
bc1q7m3vmafshmkhz29ec8tayx3704qaa8xxhhadf5
</li>
<li align="justify">Ethereum (ETH), Ethereum Classic (ETC), Callisto (CLO) or any ETH, ETC or CLO based tokens:<br>
0xBc306a88F17cb88DaDcBB80A60E8a93E9B74558c
</li>
<li align="justify">BitCoin Cash (BCH):<br>
qr6d8mjm4fr90ryyywkhs578f0lgn7e5guue964rqz
</li>
<li align="justify">BitCoin Gold (BTG):<br>
GagaV6V46oLNzuJq1RrHzQuZXB9KvQDuv7
</li>
<li align="justify">BitCoin SV (BSV):<br>
1NVRHunKywVvkh1MgMFUQLUxEFUBxPk4vy
</li>
<li align="justify">LiteCoin (LTC):<br>
LKinnpFBxf2F8ZwTivYwLRtbX99bB9qcCE
</li>
<li align="justify">Cardano (ADA):<br>
DdzFFzCqrhsnVi7hPhGzUVeoMk2xmQvN4i4uMRUi2RED8TtsVKqj4vXY3QxEC9HbVXWrequmqemHyzEQDNcX2246tSH6jQEv1cmU7yzX
</li>
<li align="justify">Stellar Lumens (XLM):<br>
GAUVDHXFDAF36IM267NW2XOHOWAUJ7VFEXSRFBCIHHLG53IZIDXRZBX5
</li>
<li align="justify">Ripple (XRP):<br>
rp4rfoceHEdpUpp8z5r5AnS27t1JMY7j3a
</li>
<li align="justify">Binance Coin (BNB):<br>
bnb1fzyxmu2f9t5dcvccjrzjpkvye7fpgd7rwlzxfk
</li>
<li align="justify">TRON (TRX), BitTorrent (BTT), WINk (WIN), Tether USDT (TRX-USDT) or any TRX based tokens:<br>
TRx67xS64bTuoVBxE67gcirhttWuZhrVTv
</li>
<li align="justify">Multi-Collateral DAI (DAI), Compound DAI (CDAI) or Old DAI (SAI):<br>
0xBc306a88F17cb88DaDcBB80A60E8a93E9B74558c
</li>
<li align="justify">DogeCoin (DOGE):<br>
DQBceUqt9tY4SXqFNf1BWVmDjQ1hRZyzs5
</li>
<li align="justify">ARK (ARK):<br>
AXGgC9t1Xk7Pcb6cjGB2cAhfkiriNnpBP3
</li>
<li align="justify">Cosmos (ATOM):<br>
cosmos1wjwzc0j8y0nj6ua63qx98y2r3d7sjdnl77zs28
</li>
<li align="justify">Dash (DASH):<br>
XdwuZTLt3uwKF25J6wPvDxKqUdESkQfqgE
</li>
<li align="justify">Decred (DCR):<br>
DsbsetxhafJQF9qu5gNs39pEq8RFDLZW64P
</li>
<li align="justify">DigiByte (DGB):<br>
DApgQ4EwJHhkG1wEGr1dCmbB8ScuWw47kG
</li>
<li align="justify">EOS (EOS), eosDAC (EOSDAC) and EOS based Tokens:<br>
gu4dkmbzhege
</li>
<li align="justify">Lisk (LSK):<br>
982485030507303108L
</li>
<li align="justify">Monero (XMR):<br>
45m8V8NCb3EDabWDpAV4UD6bXamiPAwXAEq2LGk1xGfYTxrUcB9a2Q7CHPZnkhAccMbk5WRAWHxcqV1Kc8XZ3xrCDPq6JTg
</li>
<li align="justify">Nano (NANO):<br>
nano_15kt9phu8cqnq9yfrbxosanea1uzhwi6cfb9o4m5sssnzjx8ze4fh97qrbso
</li>
<li align="justify">NEM (XEM):<br>
NDR2OOXGUB3BQUPEMW3THRJDVA2RKHQVQ2Z5YH6C
</li>
<li align="justify">NEO (NEO) and NEO Gas (GAS):<br>
AUjkYDiYNwkinqCJqhvdoyszufhjrxDRar
</li>
<li align="justify">Ontology (ONT) and Ontology Gas (ONG):<br>
ASEoXkbtnKf7k2uxF2uq8xpRugDKeMbSpN
</li>
<li align="justify">Qtum (QTUM):<br>
QbJQz4CMSFbb3UTMdho37mLJ2qHVMJv2w6
</li>
<li align="justify">RavenCoin (RVN):<br>
RQA7YVbuoVquwKUZnz4gqTqLfWmxX7euBY
</li>
<li align="justify">Tezos (XTZ):<br>
tz1RSMFcmgCC2VhLzRKEcAVbFqxjnBmVW1mR
</li>
<li align="justify">Waves (WAVES):<br>
3PJpQ2tkYwgUnSzz1NXSbEQjMuEUcULeiLg
</li>
<li align="justify">Zcash (ZEC):<br>
t1NYL2BXuaGnkScy1MZjc9XPJg5fva29dRB
</li>
<li align="justify">RSKMainNet (RBTC):<br>
0xbE3e3b4B06FD3617b0d2b256cd1Aab6159157e7a
</li>
<li align="justify">Unity (JXX):<br>
0x86FfA1eA3B5A67996f1f33Bb7BF20D0b69eCF6ae
</li>
<li align="justify">BitCore (BTX):<br>
2QeVXDYLJe85FCZDbTWfnhavsmxv65vLN2
</li>
<li align="justify">GroestlCoin (GRS):<br>
FVVvtdDPNw35cywDCDgxb8MBqArf3YSnJw
</li>
<li align="justify">Kin (KIN):<br>
GBHLFZALLF75COCK52GB4HNMRYPM2Q33XZ6H3FW5EC54S4F7IPISZHIU
</li>
</ul>
<p align="justify">
Should you wish to use digital currency, I highly recommend checking out this referral link: <a href="https://www.coinbase.com/join/turner_sep" target="_blank">Digital</a> <a href="https://www.coinbase.com/join/turner_sep" target="_blank">Currency</a>. Signing up from that <a href="https://www.coinbase.com/join/turner_sep" target="_blank">link</a> also helps The Little Engineers in the long run. If you would like to make a donation by some other means, feel free to contact me by e-mail or  FaceBook Messenger. Please note, however, that donations are completely optional, but they do help to further product development. All products developed by The Little Engineers are completely free to use under the terms of the <a href="http://www.TheLittleEngineers.org/pages/reference/20200112/CreativeCommons/CCBYSA.htm" target="_blank">Creative Commons Attribution-ShareAlike 4.0 International</a> <a href="http://www.TheLittleEngineers.org/pages/reference/20200112/CreativeCommons/CCBYSALegalCode.htm" target="_blank">(CC BY-SA 4.0)</a> License, even for commercial purposes.</p>
<p align="justify"><ul align="justify">
<li align="justify">Please consider subscribing to our <a href="https://www.youtube.com/channel/UCgAwso8p5hkLFN9AdN6oxQg" target="_blank">YouTube</a> <a href="https://www.youtube.com/channel/UCgAwso8p5hkLFN9AdN6oxQg" target="_blank">Channel:</a><br>
<a href="https://www.youtube.com/channel/UCgAwso8p5hkLFN9AdN6oxQg" target="_blank">https://www.youtube.com/channel/UCgAwso8p5hkLFN9AdN6oxQg</a></li>
<li align="justify">Please follow us on <a href="https://twitter.com/TLEngineers" target="_blank">Twitter</a>:<br><a href="https://twitter.com/TLEngineers" target="_blank">https://twitter.com/TLEngineers</a></li>
<li align="justify">Please check us out on <a href="https://www.twitch.tv/thelittleengineers" target="_blank">Twitch</a>:<br><a href="https://www.twitch.tv/thelittleengineers" target="_blank">https://www.twitch.tv/thelittleengineers</a></li>
<li align="justify">Please consider following us on <a href="https://www.instagram.com/thelittleengineers_org/" target="_blank">Instagram</a>:<br><a href="https://www.instagram.com/thelittleengineers_org/" target="_blank">https://www.instagram.com/thelittleengineers_org/</a></li>
<li align="justify">Please follow us on <a href="https://github.com/TheLittleEngineers?tab=repositories" target="_blank">GitHub</a> in order to access all of our projects:<br><a href="https://github.com/TheLittleEngineers" target="_blank">Github</a>.</li>
</ul>
<p align="justify">
Thank You for your time. I hope that you enjoy using these products as much as I enjoyed developing them (or debugging them in the case of the designs produced by my nephew and his father). - Robert &quot;The R.A.T.&quot; Allen Turner
</p>
<hr>
<!-- /Center Row -->

<!-- Bottom Left Column -->
<div class="row" style="background-color:WhiteSmoke;" align="center">
<div class="column" style="background-color:WhiteSmoke;" align="center">
<p align="center">
<h2 align="center"><font size="6">Trials and Tribulations</font></h2>
<font size="5"><em>August 5, 2019 through December 7, 2019 and beyond</em></font></h2>
<p align="justify" id="son">
*You may have noticed the asterisk (*) in the preceding text in reference to my not having seen my son for quite some time. Events to occur the week of August 5, 2019 would rectify that situation but at no small cost to me. Suffice it to say that my health took a bit of a downward turn resulting from no less than nine sets of symptoms/conditions which culminated in open heart surgery eight weeks ago (as of December 7, 2019). My son drove for many hours and stayed with me up until the day of the surgery at which time he had to return to work. Below, I have listed my discharge diagnosis which lists all nine of these in roughly the order of their occurence, keeping in mind that this all happened to me between August 2019 and November 2019.<br><br>
<center><b><big>Discharge Diagnosis:</big></b><br></center>
<ol align="justify">
<li align="justify">CHF:Congestive Heart Failure</li>
<li align="justify">RG:Reflux Gastritis including a near fatal infection resulting in colitis</li>
<li align="justify">CDD:C5/C6 Degenerative Disease</li>
<li align="justify">HTN:Hypertension</li>
<li align="justify">HLD:Hyperlipidemia</li>
<li align="justify">HM:Hypomagnasemia</li>
<li align="justify">HC:Hypocalcemia</li>
<li align="justify">CAD:Coronary Artery Disease</li>
<li align="justify">ABLA:Acute Blood Loss Anemia</li>
</ol>
<p align="justify">Now, with that being said, I am doing just fine and have recovered nicely. However, our family was struck with yet more bad news.</p>
  </div>
<!-- /Bottom Left Column -->  

<!-- Bottom Right Column -->
<div class="column" style="background-color:WhiteSmoke;" align="center">
<p align="center">
<h2><font size="6">Multiple Myeloma</font></h2>
<font size="5"><em>Cousin William Lee</em></font>
</p>
<p align="justify">
Almost two weeks into the the &quot;New Year of 2020&quot;, on the date of January 12, 2020, the family received even more bad news. My cousin William, the son of my mothers sister, was diagnosed with blood cancer, specifically multiple myeloma. His condition is terminal, although the physicians are optimistic that, with treatment, He can expect somewhere between five and ten years. This was yet another crushing blow to the family.<br><br>I suppose that my life has reached a point to where I dread the coming of each new day for the news that it may bring. However, I shall endevor to persevere whilst immersing myself into the day to day operations of &quot;<a href="http://www.RetroATX.com" target="_blank">Retro</a><u>-</u><a href="http://www.Retro-ATX.com" target="_blank">ATX</a>&quot; and &quot;<a href="http://www.TheLittleEngineers.org/" target="_blank">The Little Engineers Project</a>&quot;. I hereby extend my gratitude to one and all for your continued <a href="#digitalcurrency">support</a> and <a href="https://www.patreon.com/TheLittleEngineers" target="_blank">encouragement</a>. May God Bless You and Yours. I remain sincerely yours, <em>Robert &quot;The R.A.T.&quot; Turner</em>.
</div>
<!-- /Bottom Right Column -->
</div>
</body>
</html>

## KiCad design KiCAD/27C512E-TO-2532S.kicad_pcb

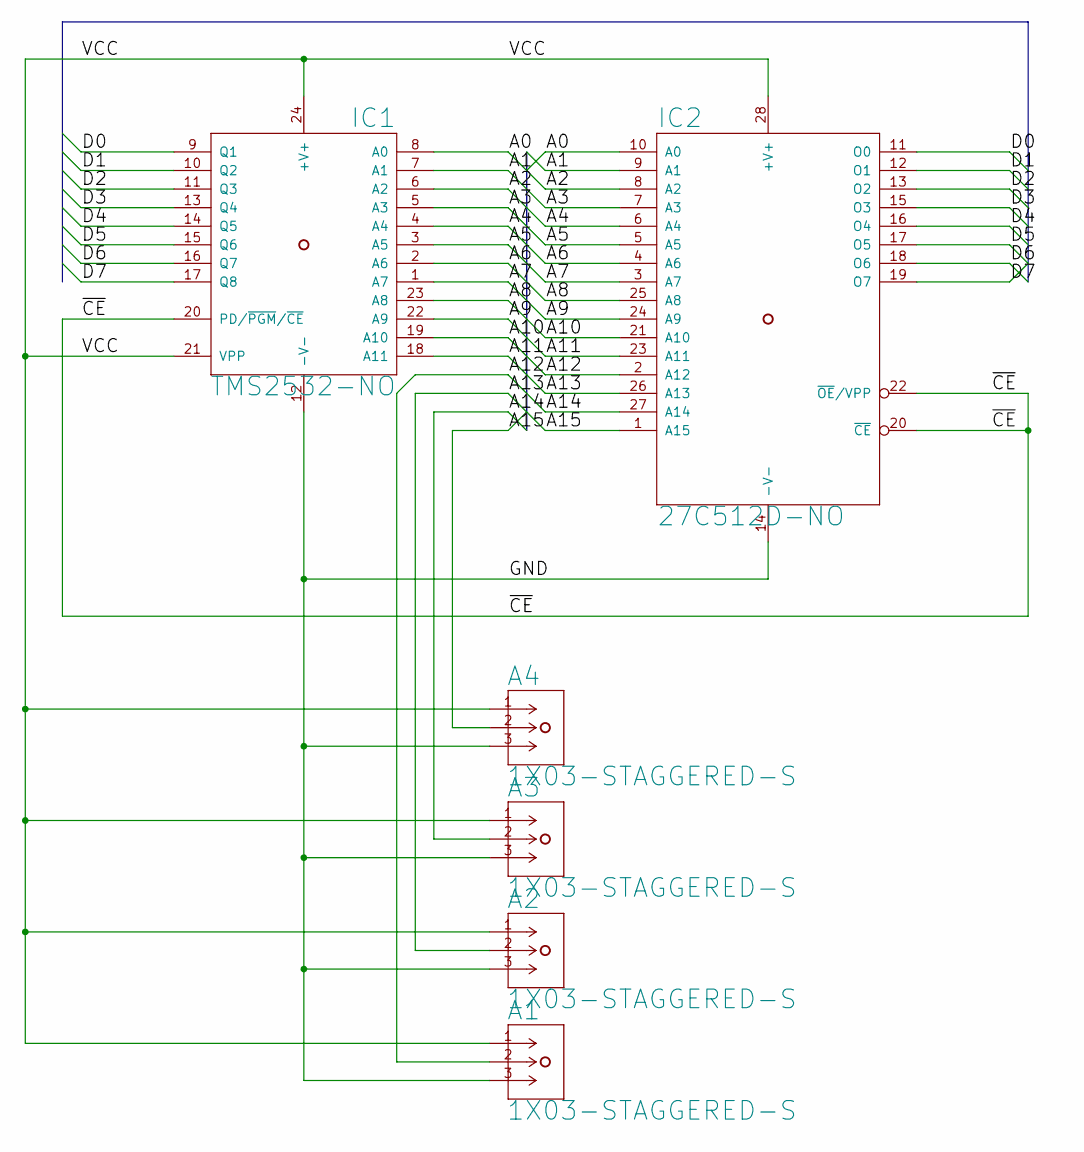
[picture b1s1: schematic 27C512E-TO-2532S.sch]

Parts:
A1, A2, A3, A4: 1X03-STAGGERED-S; 1X03-STAGGERED
IC1: TMS2532-NO; DIL24-6-NO-OUTLINE
IC2: 27C512D-NO; DIL28-6-NO-OUTLINE

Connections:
/A0: IC1.8 (A0), IC2.10 (A0)
/A1: IC1.7 (A1), IC2.9 (A1)
/A2: IC1.6 (A2), IC2.8 (A2)
/A3: IC1.5 (A3), IC2.7 (A3)
/A4: IC1.4 (A4), IC2.6 (A4)
/A5: IC1.3 (A5), IC2.5 (A5)
/A6: IC1.2 (A6), IC2.4 (A6)
/A7: IC1.1 (A7), IC2.3 (A7)
/A8: IC1.23 (A8), IC2.25 (A8)
/A9: IC1.22 (A9), IC2.24 (A9)
/A10: IC1.19 (A10), IC2.21 (A10)
/A11: IC1.18 (A11), IC2.23 (A11)
/A12: A1.2, IC2.2 (A12)
/A13: A2.2, IC2.26 (A13)
/A14: A3.2, IC2.27 (A14)
/A15: A4.2, IC2.1 (A15)
/D0: IC1.9 (Q1), IC2.11 (O0)
/D1: IC1.10 (Q2), IC2.12 (O1)
/D2: IC1.11 (Q3), IC2.13 (O2)
/D3: IC1.13 (Q4), IC2.15 (O3)
/D4: IC1.14 (Q5), IC2.16 (O4)
/D5: IC1.15 (Q6), IC2.17 (O5)
/D6: IC1.16 (Q7), IC2.18 (O6)
/D7: IC1.17 (Q8), IC2.19 (O7)
/GND: A1.3, A2.3, A3.3, A4.3, IC1.12 (-V-), IC2.14 (-V-)
/VCC: A1.1, A2.1, A3.1, A4.1, IC1.21 (VPP), IC1.24 (+V+), IC2.28 (+V+)
/~CE: IC1.20 (PD/~PGM~/~CE), IC2.20 (~CE), IC2.22 (~OE~/VPP)

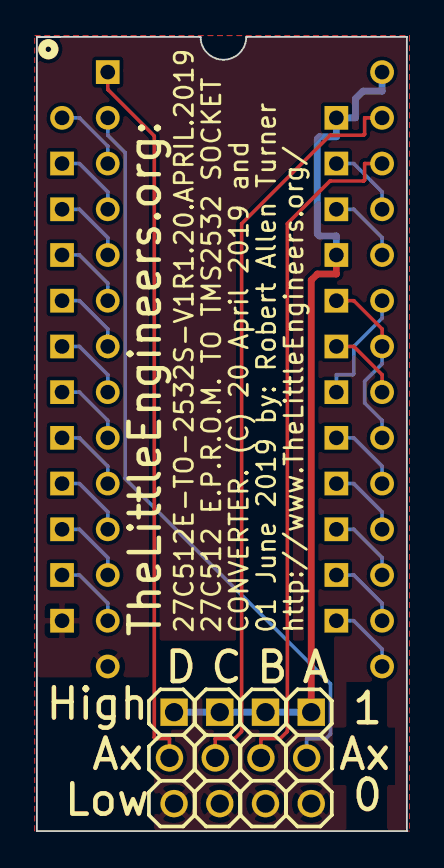
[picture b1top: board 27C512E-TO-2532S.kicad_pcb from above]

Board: 2 copper layers, 20.6 x 44.1 mm, 7 parts (0 on the bottom side), 27 nets.

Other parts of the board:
U$1: OUTLINE

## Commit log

2019-07-31 Added DIRectories for better organization and optimization
2019-08-01 Maintenance

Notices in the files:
parts and their libraries:
Copyright ©07 Jan 2013, by: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
Copyright ©01 Jun 2019, by: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
